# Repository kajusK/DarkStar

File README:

Jakub Kaderka
jakub.kaderka@gmail.com
2015

Led headlamp based on PIC 16F616

=============================
Basic principle
=============================

PIC works as core of DC-DC step down converter. It has two internal independent
comparators which compare voltage on led sense resistor with a reference voltage
generated by PWM. The switching frequency is set by an external RC circuit to
about 100kHz.

The PIC generates two channel PWM signal (one for each led) which creates a
reference voltage after reducing the level by rezistor divider and smoothing
by RC circuit.

=============================
Implementation
=============================

The PWM is generated by software during interrupt routine (tmr0 overflows every
1ms). To keep it short and simple, the routine generates a shorter part of the
pulse. This way up to 50% of the system time is used for generator

If the PWM duty is over 50%, generate low part, if less than 50% generate high.

The rest of the programming is divided into two tasks: Key task and ADC task

--------------
Key task
--------------
Called every 10ms, it check the current key states and sets the flags. It's able
to detect two key press lengths. Short press and long press. The long press
generates two separate handler calls, first is generated when time the key
is pressed exceeds the long press threshold and the second event occurs when
the key is released.

Key handlers points to actions.asm file which contains definitions of led modes
etc.

--------------
ADC task
--------------
ADC task is called every 200ms, it checks the battery voltage and corrects
the PWM output to keep the reference voltage stable when the supply voltage
drops.

The way the voltage is measured is a little tricky, to keep the consumed power
during sleep as low as possible, the pic uses a status LED as a reference which
brings kind of reversed logic into the program.

When device goes to sleep, status led is turned off and consumes no power.

When the supply voltage drops, the voltage across led is kept at the same level.
Because PIC takes the supply voltage as a reference for AD module, the measured
AD data on LED are getting bigger as the voltage drops. The equations how to
calculate the voltage from AD data are discussed in more details in ad.asm

Anyway this solutions has also some disadvantages. Due to low pin count and
quite crowded PCB, it's connected between pwm output and one of the pins.
As the pwm output changes quite often, the interrupt must be disabled during
measurement, therefore ADC task cannot be called very often as it would make
pwm output quite unstable.

The second problem is that the voltage across LED is not 100% stable, it changes
a bit as the input voltage drops. To set the threshold correctly, the actual
voltage at 3V needs to be measured and used in calculations

=============================
Operations
=============================
After connecting device to power, it goes to sleep. Press bt1 for about 2 sec to
turn it on. Press it again for more than 2 sec to turn it off

Press bt2 for about 2 sec to activate/deactivate second led.

Short press of bt1 increases light output, bt2 decreases
Led1 is turned on all times except the power off state, led2 is controled by
long press of bt2 (on/off), long press bt2 also switches currently controled
led's intensity

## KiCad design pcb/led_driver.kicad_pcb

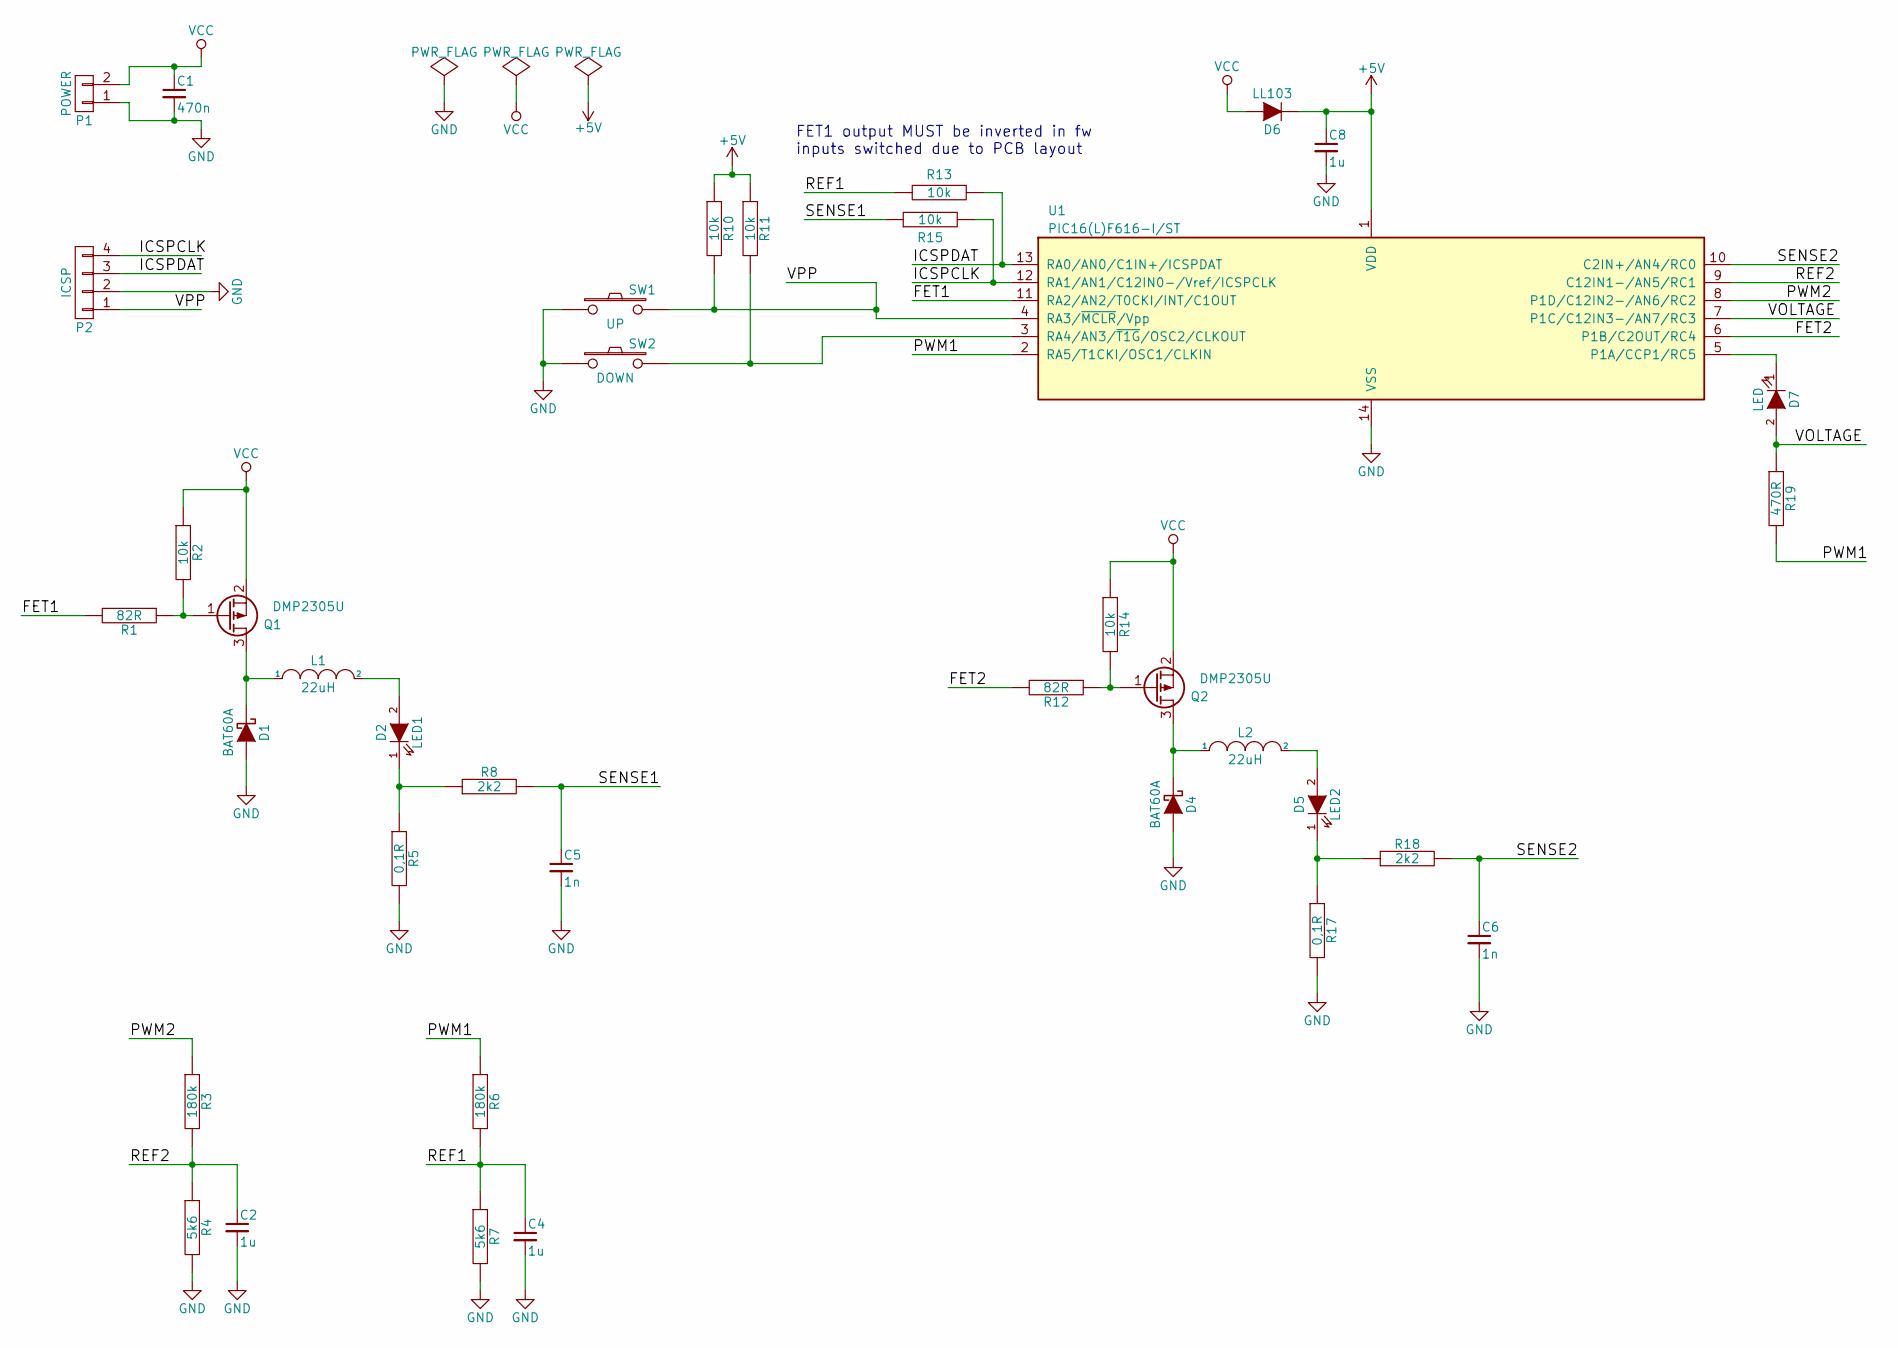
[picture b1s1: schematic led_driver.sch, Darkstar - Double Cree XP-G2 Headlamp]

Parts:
C1: 470n; C_0805
C2, C4, C8: 1u; C_0805
C5, C6: 1n; C_0805
D1, D4: BAT60A; SOD-323
D2: LED1; LED-XP-G_CREE
D5: LED2; LED-XP-G_CREE
D6: LL103; Diode-MiniMELF_Standard
D7: LED; LED-0805
L1, L2: 22uH; Choke_SMD_Wuerth-WE-PD2-Typ-MS
P1: POWER; GS2
P2: ICSP; SOT-143
Q1, Q2: DMP2305U; SOT-23_Handsoldering
R1, R12: 82R; R_0805
R2, R10, R11, R14: 10k; R_0805
R3, R6: 180k; R_0805
R4, R7: 5k6; R_0805
R5, R17: 0,1R; R_1206
R8, R18: 2k2; R_0805
R13, R15: 10k; R_1206
R19: 470R; R_0805
SW1: UP; SW_SPST_FSMSM
SW2: DOWN; SW_SPST_FSMSM
U1: PIC16(L)F616-I/ST; TSSOP-14_4.4x5mm_Pitch0.65mm

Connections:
+5V: C8.1, D6.1 (K), R10.1, R11.1, U1.1 (VDD)
/FET1: R1.2, U1.11 (RA2/AN2/T0CKI/INT/C1OUT)
/FET2: R12.2, U1.6 (P1B/C2OUT/RC4)
/HEATSINK: D2.3, D5.3
/ICSPCLK: P2.4, R15.2, U1.12 (RA1/AN1/C12IN0-/Vref/ICSPCLK)
/ICSPDAT: P2.3, R13.1, U1.13 (RA0/AN0/C1IN+/ICSPDAT)
/PWM1: R6.1, R19.2, U1.2 (RA5/T1CKI/OSC1/CLKIN)
/PWM2: R3.1, U1.8 (P1D/C12IN2-/AN6/RC2)
/REF1: C4.1, R6.2, R7.1, R13.2
/REF2: C2.1, R3.2, R4.1, U1.9 (C12IN1-/AN5/RC1)
/SENSE1: C5.1, R8.2, R15.1
/SENSE2: C6.1, R18.2, U1.10 (C2IN+/AN4/RC0)
/VOLTAGE: D7.2 (A), R19.1, U1.7 (P1C/C12IN3-/AN7/RC3)
/VPP: P2.1, R10.2, SW1.2, U1.4 (RA3/~MCLR~/Vpp)
GND: C1.2, C2.2, C4.2, C5.2, C6.2, C8.2, D1.2 (A), D4.2 (A), P1.1, P2.2, R4.2, R5.2, R7.2, R17.2, SW1.1, SW2.1, U1.14 (VSS)
unnamed: D1.1 (K), L1.1, Q1.3 (D)
unnamed: D2.1 (K), R5.1, R8.1
unnamed: D2.2 (A), L1.2
unnamed: D4.1 (K), L2.1, Q2.3 (D)
unnamed: D5.1 (K), R17.1, R18.1
unnamed: D5.2 (A), L2.2
unnamed: D7.1 (K), U1.5 (P1A/CCP1/RC5)
unnamed: Q1.1 (G), R1.1, R2.2
unnamed: Q2.1 (G), R12.1, R14.2
unnamed: R11.2, SW2.2, U1.3 (RA4/AN3/~T1G~/OSC2/CLKOUT)
VCC: C1.1, D6.2 (A), P1.2, Q1.2 (S), Q2.2 (S), R2.1, R14.1

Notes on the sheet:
FET1 output MUST be inverted in fw inputs switched due to PCB layout

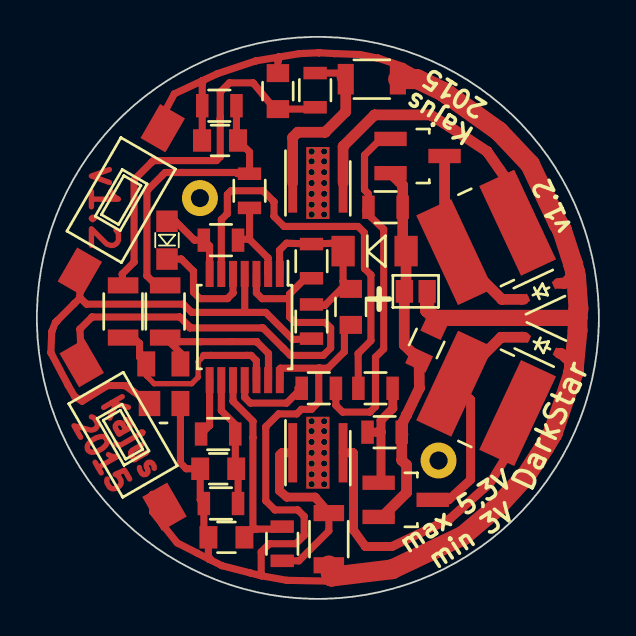
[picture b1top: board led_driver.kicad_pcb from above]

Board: 2 copper layers, 31.2 x 31.2 mm, 38 parts (0 on the bottom side), 26 nets.

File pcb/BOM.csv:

Reference, Value, Footprint,Supplier
C1,470n,Capacitors_SMD:C_0805,
C2,1u,Capacitors_SMD:C_0805,
C4,1u,Capacitors_SMD:C_0805,
C5,1n,Capacitors_SMD:C_0805,
C6,1n,Capacitors_SMD:C_0805,
C8,1u,Capacitors_SMD:C_0805,
D1,BAT60A,Diodes_SMD:SOD-323,http://cz.farnell.com/infineon/bat-60a-e6327/rectifier-schot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
D4,BAT60A,Diodes_SMD:SOD-323,http://cz.farnell.com/infineon/bat-60a-e6327/rectifier-schot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
D7,LED,LEDs:LED-0805,http://cz.farnell.com/multicomp/ovs-0808/led-0805-super-brt-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
D2,LED1,LEDs:LED-XP-G_CREE,http://cz.farnell.com/cree/xpgwht-0-1-0000-00gc2/led-od-wht-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
D5,LED2,LEDs:LED-XP-G_CREE,http://cz.farnell.com/cree/xpgwht-0-1-0000-00gc2/led-od-wht-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
D6,LL103,Diodes_SMD:Diode-MiniMELF_Standard,http://cz.farnell.com/vishay-semiconductor/ll103a-gs08/diode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
L1,22uH,Choke_SMD:Choke_SMD_Wuerth-WE-PD2-Typ-MS,http://cz.farnell.com/bourns/srn6045-220m/inductor-power-22u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
L2,22uH,Choke_SMD:Choke_SMD_Wuerth-WE-PD2-Typ-MS,http://cz.farnell.com/bourns/srn6045-220m/inductor-power-22u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
P1,POWER,Connect:GS2,
P2,ICSP,Housings_SOT-23_SOT-143_TSOT-6:SOT-143,
Q1,DMP2305U,Housings_SOT-23_SOT-143_TSOT-6:SOT-23_Handsoldering,http://cz.farnell.com/diodes-inc/dmp2305u-7/mosfet-p-ch-20v-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
Q2,DMP2305U,Housings_SOT-23_SOT-143_TSOT-6:SOT-23_Handsoldering,http://cz.farnell.com/diodes-inc/dmp2305u-7/mosfet-p-ch-20v-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
R17,0R1,Resistors_SMD:R_1206,
R5,0R1,Resistors_SMD:R_1206,
R10,10k,Resistors_SMD:R_0805,
R11,10k,Resistors_SMD:R_0805,
R13,10k,Resistors_SMD:R_1206,
R14,10k,Resistors_SMD:R_0805,
R15,10k,Resistors_SMD:R_1206,
R2,10k,Resistors_SMD:R_0805,
R3,180k,Resistors_SMD:R_0805,
R6,180k,Resistors_SMD:R_0805,
R18,2k2,Resistors_SMD:R_0805,
R8,2k2,Resistors_SMD:R_0805,
R19,470R,Resistors_SMD:R_0805,
R4,5k6,Resistors_SMD:R_0805,
R7,5k6,Resistors_SMD:R_0805,
R1,82R,Resistors_SMD:R_0805,
R12,82R,Resistors_SMD:R_0805,
SW1,UP,Buttons_Switches_SMD:SW_SPST_FSMSM,http://cz.farnell.com/te-connectivity-alcoswitch/fsmsm/switc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
SW2,DOWN,Buttons_Switches_SMD:SW_SPST_FSMSM,http://cz.farnell.com/te-connectivity-alcoswitch/fsmsm/switc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
U1,PIC16(L)F616-I/ST,Housings_SSOP:TSSOP-14_4.4x5mm_Pitch0.65mm,http://cz.farnell.com/microchip/pic16f616-i-st/mcu-8bit-pic1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

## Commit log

2015-07-06 first pwm routine
2015-07-06 Somehow working pwm
2015-07-12 Pwm working, ad code added
2015-07-24 PWM and led control works
2015-07-26 Led modes + buttons working, ad disabled
2015-07-28 All basic stuff works
2015-07-29 Everything works, code cleaned
2015-07-29 Readme added
2015-07-29 added pcb design
2015-07-29 3D drawing added
2015-09-25 Latest pcb design, leds still on main board
2015-11-30 Comments in schematic changed
2015-12-01 Fixed missing footprint error
2015-12-01 Removed backup files
2015-12-01 Thermal vias added
2015-12-03 Cleanup, preparing for manufacturing
2015-12-07 Cleanup before sending to seedstudio
2015-12-08 Divider modified for higher stability and overcurrent protection on fw error
2016-01-10 Renamed gerber extension to required form by manufacturer
2016-01-10 Fixed resistor not in E12
2016-02-10 Created directory for multiple cad parts
2016-02-10 Bill of material added
2016-02-11 Pic readme converted to markdown
2016-02-15 fixed MCU name in sources
2016-02-15 License and Readme added
2016-02-15 Fixed comment in schematics
2016-02-15 Added pdf schema
2016-02-16 Holes resized to match recommended diameter for screw taps
2016-02-16 Added HowTos to Readme
2016-02-16 added control knob
2016-02-16 removed uneeded cad files
2016-02-16 Added line wraps at 80 characters
2016-02-16 Added some images
2016-03-19 Cleanup, fixing typos...
2016-03-19 Corrected control knob dimensions to match prototype
2016-03-21 Added battery box body
2016-03-25 Turn off adc during standby
2016-03-25 Switched to 8MHz for more stable light output
2016-03-25 Added low power mode before power off
2016-03-25 Updated readme to reflect low level mode changes
2016-03-26 Added body drawings, incomplete
2016-03-28 Improved brightness stepping
2016-03-28 Longer period for AD measurements
2016-03-31 Some updates to cad drawings
2016-04-02 Added max PWM limit
2016-04-07 Driver pcb moved to separate folder
2016-04-09 Added switch model
2016-05-05 added battery box lid
2016-05-05 Returned pcb to single directory
2016-05-06 Added screw knob for battery box
2016-05-23 Updated battery box knob
2016-05-23 Added recent images
2016-06-03 Increased lid depth for bigger connector
2016-06-21 Added bill of materials
2016-06-21 Added lab measurement data
2016-06-21 Chages semicollons to commas in measurement csv
2016-06-22 Updated BOM
2016-06-22 Added missing parts to BOM
2016-06-26 Updated weight and runtimes info
2016-06-29 Drawings moved to separate folder
2016-06-29 Added lamp holder
2016-07-14 Added finished photo on helmet
2017-04-30 Fixed o-ring dimension
2018-11-25 Added link to new version
